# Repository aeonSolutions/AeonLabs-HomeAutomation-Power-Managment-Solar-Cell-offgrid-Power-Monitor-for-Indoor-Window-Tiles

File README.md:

[PCB-Prototyping-Catalogue](https://github.com/aeonSolutions/PCB-Prototyping-Catalogue)  >>  [Home-Automation](https://github.com/aeonSolutions/PCB-Prototyping-Catalogue/tree/main/Home-Automation)  >>  [Smart Home Solar Power Management](https://github.com/aeonSolutions/PCB-Prototyping-Catalogue/tree/main/Home-Automation/Smart%20Home%20Solar%20Power%20Management)  >>   Solar Cell Tiles Power Monitor for Indoor Windows

<br>

<br />

# Solar Cell Tiles Power Monitor for Indoor Windows

This is a simple PCB for a direct fit on commercially available [blue solar cell tiles](https://s.click.aliexpress.com/e/_DCnJW0V)  with dimensions 124x124mm. This Smart Device is intended to connected with the [Single Solar Cell with one 18650 Battery Storage](https://github.com/aeonSolutions/AeonLabs-HomeAutomation-Power-Managment-Single-SolarCELL-18650-battery-storage/blob/main/README.md) and also the [Single Solar Cell with two 18650 as Battery Storage](https://github.com/aeonSolutions/AeonLabs-HomeAutomation-Power-Managment-Single-SolarCELL-2X-18650-battery-storage/blob/main/README.md) to do active solar cell tile and battery management up to 8 solar tiles conencted together intended for indoor usage. In particular to be installed on the top or downside of transparent glass windows at a home or office. This PCB, when assembled with a blue solar cell tile, can be used to power a low voltage 4.2V indoor illumination network using ultra-low power micro LED strips.  For insatnce [this one](https://s.click.aliexpress.com/e/_DCKg9xJ) sold on AliExpress.   

When connected in series and installed on several windows and networked, can power off the grid a 4.2V LED illumination on all rooms and compartments at a home or office. During evenings and at night until bedtime. If one intends to use it to power indoors LED illumination during the day is required a High Capacity Power Bank connected to all first tiles of all the series. For instance this [power bank](https://s.click.aliexpress.com/e/_Ddl7nsh) here. 

One important take way about this prototype project is in the ability to be installed on any traditional apartment or home in a big city, requiring  124mm of window glass estate, at the top or at the bottom. And it can connect to existing home automation network or systems. 

<p align="center">

</p>

A breif view of specifications:

- up to 8 solar cell tiles battery active monitoring 
- Buzzer for sound alarm and warnings
- Onboard Temperature and humidity sensores
- Onboard motion sensor
- PCB asssembly in series made with a 10 pin pin header/ socket. For "plug and play" type of instalations
- Screw terminal to connect main low power 5V DC line at home/office. 

<br>

**Status**

waiting to be tested. Stay tuned for updates.

<br>

## PCB

<br>

## Compatibility

<p align="center">

</p>

<br>

## What one additionally needs
-  home tools
-  [transparent double sided tape](https://s.click.aliexpress.com/e/_DDJxMmD)
-  [blue solar cell tiles](https://s.click.aliexpress.com/e/_DCnJW0V)
-  [ultra-low power micro LED strips](https://s.click.aliexpress.com/e/_DCKg9xJ) 
-  [ultra-low power  LED Cob strips](https://s.click.aliexpress.com/e/_DnqkC4N)
-  [Nylon Guide for Electric Cable](https://s.click.aliexpress.com/e/_DBc1oVX)
-  [NCR18650B 3.7V 3400 mah 18650 Lithium](https://s.click.aliexpress.com/e/_DCh1sw1)
-  [Low power electrical wire](https://s.click.aliexpress.com/e/_DB1T3eN)
-  [16A Electrical Plug Wall Socket 110~250V Dual USB 2000mA Port](https://s.click.aliexpress.com/e/_DlVz3sh)
-  [Soldering iron](https://s.click.aliexpress.com/e/_DnDN8x3)
-  [Solder](https://s.click.aliexpress.com/e/_DlXtKMN)
- [power bank](https://s.click.aliexpress.com/e/_Ddl7nsh) 

<br />
<br />

## Author

You can get in touch with me on my LinkedIn Profile:

#### Miguel Tomas

You can also follow my GitHub Profile to stay updated about my latest projects: 

<br>

### Be supportive of my dedication and work towards technology education and buy me a cup of coffee
The PCB Desgin Files i provide here for anyone to use are free. If you like this Smart Device or use it, please consider buying me a cup of coffee, a slice of pizza or a book to help me study, eat and think new PCB design files.

<br />

### Make a donation on Paypal
Make a donation on paypal and get a TAX refund*.

<br>

### Support all these open hardware projects and become a patreon  
Liked any of my PCB KiCad Designs? Help and Support my open work to all by becomming a LDAD Patreon.
In return I will give a free PCB design in KiCad to all patreon supporters. To learn more go to patreon.com. Link below.

<br />
<br />

______________________________________________________________________________________________________________________________
### License
Before proceeding to download any of AeonLabs software solutions for open-source development and/or PCB hardware electronics development make sure you are choosing the right license for your project. See [AeonLabs Solutions for Open Hardware & Source Development](https://github.com/aeonSolutions/PCB-Prototyping-Catalogue/wiki/AeonLabs-Solutions-for-Open-Hardware-&-Source-Development) for more information.

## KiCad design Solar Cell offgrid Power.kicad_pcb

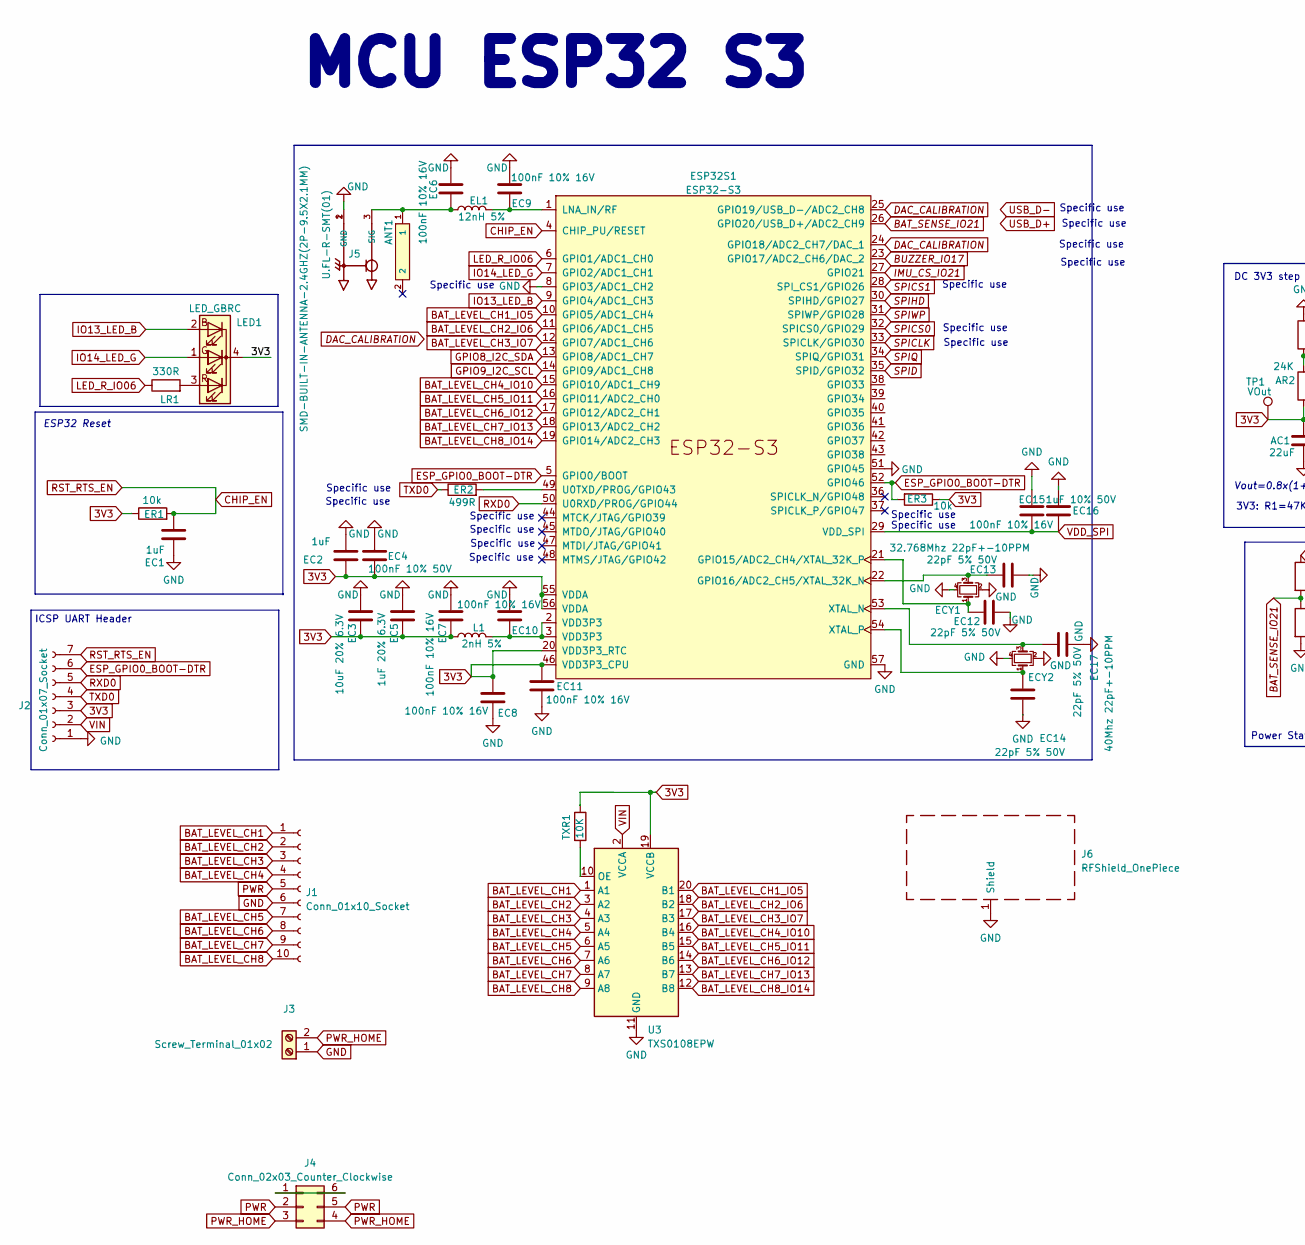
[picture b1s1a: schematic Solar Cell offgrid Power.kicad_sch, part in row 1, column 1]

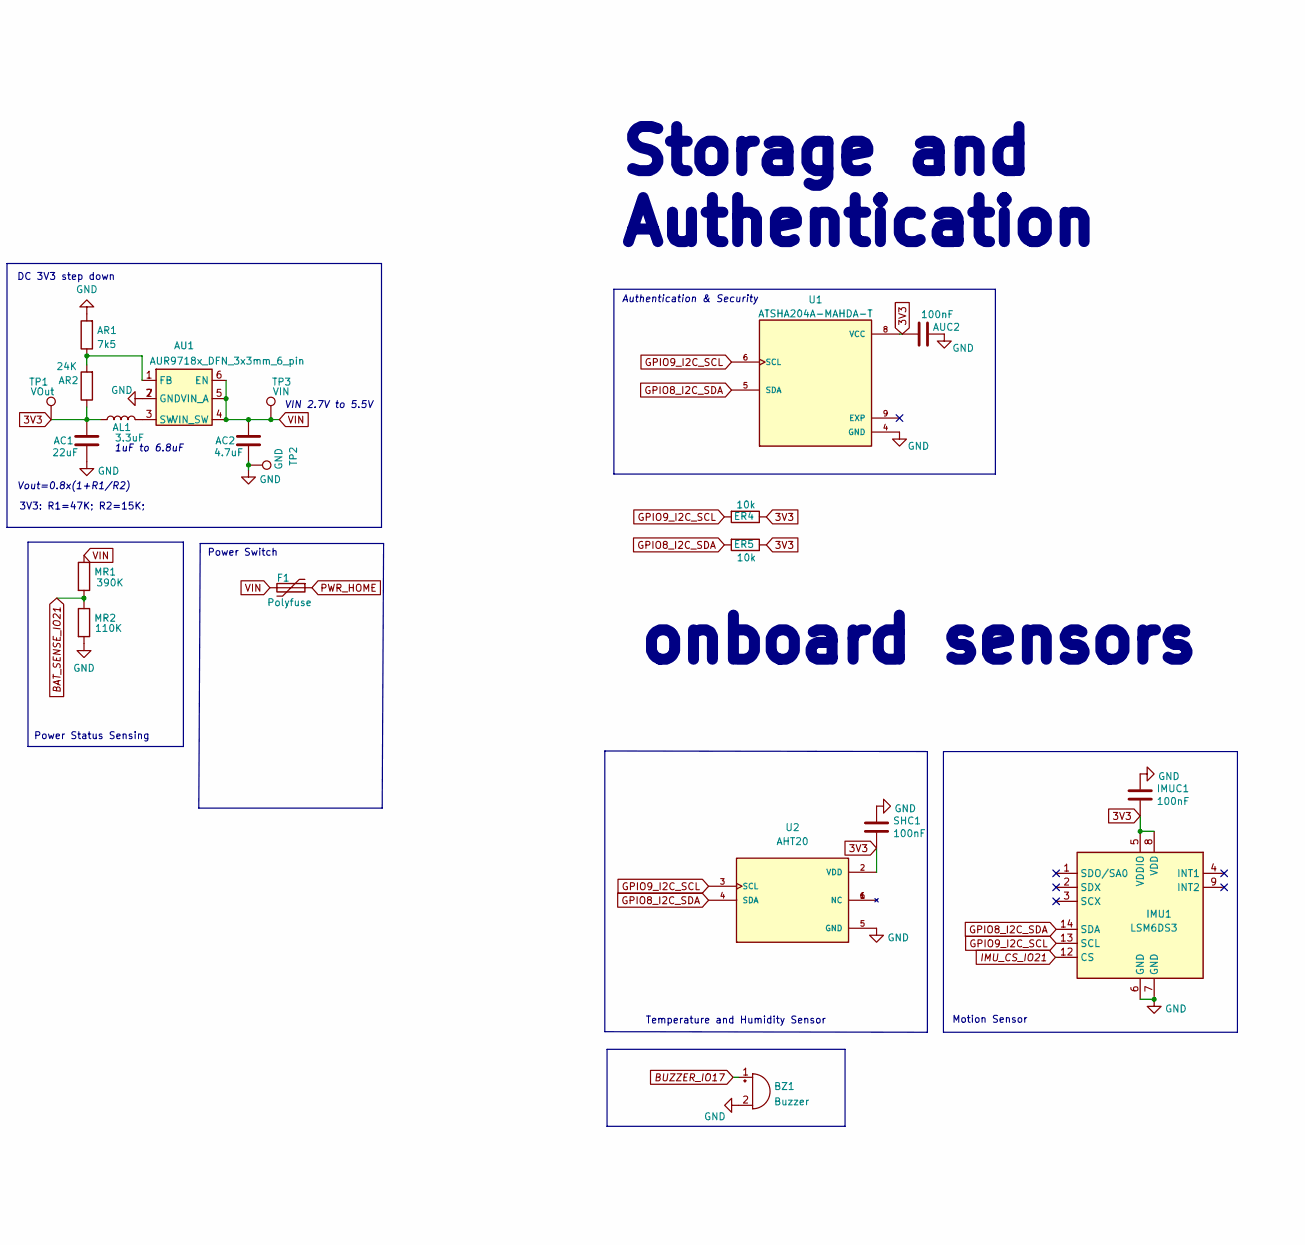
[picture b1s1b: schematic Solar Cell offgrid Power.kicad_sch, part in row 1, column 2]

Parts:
AC1: 22uF; C_0805_2012Metric_Pad1.18x1.45mm_HandSolder
AC2: 4.7uF; C_0805_2012Metric_Pad1.18x1.45mm_HandSolder
AL1: 3.3uF; L_1210_3225Metric
ANT1: SMD-BUILT-IN-ANTENNA-2.4GHZ(2P-9.5X2.1MM); 2.4ghZ WIFI ANTENNA AN9520_ANT2-SMD-9.5X2.1X1.0MM
AR1: 7k5; R_0805_2012Metric_Pad1.20x1.40mm_HandSolder
AR2: 24K; R_0805_2012Metric_Pad1.20x1.40mm_HandSolder
AU1: AUR9718x_DFN_3x3mm_6_pin; AUR9718 ST1S09 SON95P300X300X100-7N
AUC2: 100nF; C_0603_1608Metric
BZ1: Buzzer; MagneticBuzzer_Kobitone_254-EMB84Q-RO
EC1: 1uF; C_0603_1608Metric
EC2: 1uF; C_0805_2012Metric
EC3: 10uF 20% 6.3V; C_0805_2012Metric
EC4: 100nF 10% 50V; C_0603_1608Metric
EC5: 1uF 20% 6.3V; C_0603_1608Metric
EC6, EC7, EC8, EC9, EC10, EC11, EC15: 100nF 10% 16V; C_0603_1608Metric
EC12, EC13, EC14, EC17: 22pF 5% 50V; C_0603_1608Metric
EC16: 1uF 10% 50V; C_0603_1608Metric
ECY1: 32.768Mhz 22pF+-10PPM; Crystal_SMD_EuroQuartz_MT-4Pin_3.2x2.5mm
ECY2: 40Mhz 22pF+-10PPM; Crystal_SMD_EuroQuartz_MT-4Pin_3.2x2.5mm
EL1: 12nH 5%; L_0805_2012Metric
ER1, ER3, ER4, ER5: 10k; R_0603_1608Metric
ER2: 499R; R_0603_1608Metric
ESP32S1: ESP32-S3; QFN-56-1EP_7x7mm_P0.4mm_EP5.6x5.6mm
F1: Polyfuse; Fuse_1206_3216Metric_Pad1.42x1.75mm_HandSolder
IMU1: LSM6DS3; LSM6DS3 Motion Sensor PQFN50P300X250X86-14N
IMUC1: 100nF; C_0603_1608Metric
J1: Conn_01x10_Socket; PinSocket_1x10_P2.54mm_Horizontal
J2: Conn_01x07_Socket; JST_SH_SM07B-SRSS-TB_1x07-1MP_P1.00mm_Horizontal
J3: Screw_Terminal_01x02; TerminalBlock_Phoenix_MPT-0,5-2-2.54_1x02_P2.54mm_Horizontal
J4: Conn_02x03_Counter_Clockwise; Toggle Switch 2 pos PCB MSS-22D18G2 2P2T
J5: U.FL-R-SMT(01); RF Antenna IPEX SMD PCB HRS_U.FL-R-SMT(01)
J6: RFShield_OnePiece; ESP32-S3 GND Shield
L1: 2nH 5%; L_0805_2012Metric
LED1: LED_GBRC; LED_1206_3210_RGB_Metric
LR1: 330R; R_0603_1608Metric
MR1: 390K; R_0603_1608Metric
MR2: 110K; R_0603_1608Metric
SHC1: 100nF; C_0603_1608Metric
TP1: VOut; TestPoint_Pad_D1.0mm
TP2: GND; TestPoint_Pad_D1.0mm
TP3: VIN; TestPoint_Pad_D1.0mm
TXR1: 10K; R_0603_1608Metric
U1: ATSHA204A-MAHDA-T; ATSHA204A Auth SOIC8; PART_REV A
U2: AHT20; AHT20 HT Sensor PSON100P300X300X110-6N; PARTREV V1.0
U3: TXS0108EPW; TSSOP-20_4.4x6.5mm_P0.65mm

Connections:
3V3: AC1.1, AL1.1, AR2.1, EC2.2, EC3.1, EC4.2, EC5.1, EC7.1, EC8.1, EC11.1, ER1.1, ER3.1, ER4.1, ER5.1, ESP32S1.20 (VDD3P3_RTC), ESP32S1.46 (VDD3P3_CPU), ESP32S1.55 (VDDA), ESP32S1.56 (VDDA), IMU1.5 (VDDIO), IMU1.8 (VDD), IMUC1.2, J2.3, L1.1, LED1.4 (K), SHC1.2, TP1.1, TXR1.1, U1.8 (VCC), U2.2 (VDD), U3.19 (VCCB)
BAT_LEVEL_CH1: J1.1, U3.1 (A1)
BAT_LEVEL_CH1_IO5: ESP32S1.10 (GPIO5/ADC1_CH4), U3.20 (B1)
BAT_LEVEL_CH2: J1.2, U3.3 (A2)
BAT_LEVEL_CH2_IO6: ESP32S1.11 (GPIO6/ADC1_CH5), U3.18 (B2)
BAT_LEVEL_CH3: J1.3, U3.4 (A3)
BAT_LEVEL_CH3_IO7: ESP32S1.12 (GPIO7/ADC1_CH6), U3.17 (B3)
BAT_LEVEL_CH4: J1.4, U3.5 (A4)
BAT_LEVEL_CH4_IO10: ESP32S1.15 (GPIO10/ADC1_CH9), U3.16 (B4)
BAT_LEVEL_CH5: J1.7, U3.6 (A5)
BAT_LEVEL_CH5_IO11: ESP32S1.16 (GPIO11/ADC2_CH0), U3.15 (B5)
BAT_LEVEL_CH6: J1.8, U3.7 (A6)
BAT_LEVEL_CH6_IO12: ESP32S1.17 (GPIO12/ADC2_CH1), U3.14 (B6)
BAT_LEVEL_CH7: J1.9, U3.8 (A7)
BAT_LEVEL_CH7_IO13: ESP32S1.18 (GPIO13/ADC2_CH2), U3.13 (B7)
BAT_LEVEL_CH8: J1.10, U3.9 (A8)
BAT_LEVEL_CH8_IO14: ESP32S1.19 (GPIO14/ADC2_CH3), U3.12 (B8)
BAT_SENSE_IO21: ESP32S1.26 (GPIO20/USB_D+/ADC2_CH9), MR1.2, MR2.1
BUZZER_IO17: BZ1.1 (-), ESP32S1.23 (GPIO17/ADC2_CH6/DAC_2)
CHIP_EN: EC1.2, ER1.2, ESP32S1.4 (CHIP_PU/RESET), J2.7
DAC_CALIBRATION: ESP32S1.24 (GPIO18/ADC2_CH7/DAC_1), ESP32S1.25 (GPIO19/USB_D-/ADC2_CH8)
ESP_GPIO0_BOOT-DTR: ER3.2, ESP32S1.5 (GPIO0/BOOT), ESP32S1.52 (GPIO46), J2.6
GND: AC1.2, AC2.2, AR1.2, AU1.2 (GND), AU1.7 (GND), BZ1.2 (+), EC1.1, EC2.1, EC3.2, EC4.1, EC5.2, EC6.2, EC7.2, EC8.2, EC9.2, EC10.2, EC11.2, EC12.2, EC13.2, EC14.2, EC17.2, ECY1.2, ECY1.4, ECY2.2, ECY2.4, ESP32S1.8 (GPIO3/ADC1_CH2), ESP32S1.51 (GPIO45), ESP32S1.57 (GND), IMU1.6 (GND), IMU1.7 (GND), IMUC1.1, J1.6, J2.1, J3.1, J5.1 (GND), J5.2 (GND), J6.1 (Shield), MR2.2, SHC1.1, TP2.1, U1.4 (GND), U2.5 (GND), U3.11 (GND)
GPIO8_I2C_SDA: ER5.2, ESP32S1.13 (GPIO8/ADC1_CH7), IMU1.14 (SDA), U1.5 (SDA), U2.4 (SDA)
GPIO9_I2C_SCL: ER4.2, ESP32S1.14 (GPIO9/ADC1_CH8), IMU1.13 (SCL), U1.6 (SCL), U2.3 (SCL)
IMU_CS_IO21: ESP32S1.27 (GPIO21), IMU1.12 (CS)
IO13_LED_B: ESP32S1.9 (GPIO4/ADC1_CH3), LED1.2 (BA)
IO14_LED_G: ESP32S1.7 (GPIO2/ADC1_CH1), LED1.1 (GA)
LED_R_IO06: ESP32S1.6 (GPIO1/ADC1_CH0), LR1.1
unnamed: AR1.1, AR2.2, AU1.1 (FB)
unnamed: AL1.2, AU1.3 (SW)
unnamed: EC10.1, ESP32S1.2 (VDD3P3), ESP32S1.3 (VDD3P3), L1.2
unnamed: EC12.1, ECY1.1, ESP32S1.21 (GPIO15/ADC2_CH4/XTAL_32K_P)
unnamed: EC13.1, ECY1.3, ESP32S1.22 (GPIO16/ADC2_CH5/XTAL_32K_N)
unnamed: EC9.1, EL1.2, ESP32S1.1 (LNA_IN/RF)
unnamed: ER2.2, ESP32S1.49 (U0TXD/PROG/GPIO43)
unnamed: EC17.1, ECY2.3, ESP32S1.53 (XTAL_N)
unnamed: EC14.1, ECY2.1, ESP32S1.54 (XTAL_P)
unnamed: J4.1, J4.6
unnamed: ANT1.1, EC6.1, EL1.1, J5.3 (SIG)
unnamed: LED1.3 (RA), LR1.2
unnamed: TXR1.2, U3.10 (OE)
PWR: J1.5, J4.2, J4.5
PWR_HOME: F1.1, J3.2, J4.3, J4.4
RXD0: ESP32S1.50 (U0RXD/PROG/GPIO44), J2.5
SPICLK: ESP32S1.33 (SPICLK/GPIO30)
SPICS0: ESP32S1.32 (SPICS0/GPIO29)
SPICS1: ESP32S1.28 (SPI_CS1/GPIO26)
SPID: ESP32S1.35 (SPID/GPIO32)
SPIHD: ESP32S1.30 (SPIHD/GPIO27)
SPIQ: ESP32S1.34 (SPIQ/GPIO31)
SPIWP: ESP32S1.31 (SPIWP/GPIO28)
TXD0: ER2.1, J2.4
VDD_SPI: EC15.1, EC16.1, ESP32S1.29 (VDD_SPI)
VIN: AC2.1, AU1.4 (VIN_SW), AU1.5 (VIN_A), AU1.6 (EN), F1.2, J2.2, MR1.1, TP3.1, U3.2 (VCCA)

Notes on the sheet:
Specific use
Vout=0.8x(1+R1/R2)
onboard sensors
3V3: R1=47K; R2=15K;
Power Status Sensing
DC 3V3 step down
ESP32 Reset
Authentication & Security
Storage and Authentication
VIN 2.7V to 5.5V
Temperature and Humidity Sensor
Power Switch
ICSP UART Header
1uF to 6.8uF
MCU ESP32 S3
Motion Sensor

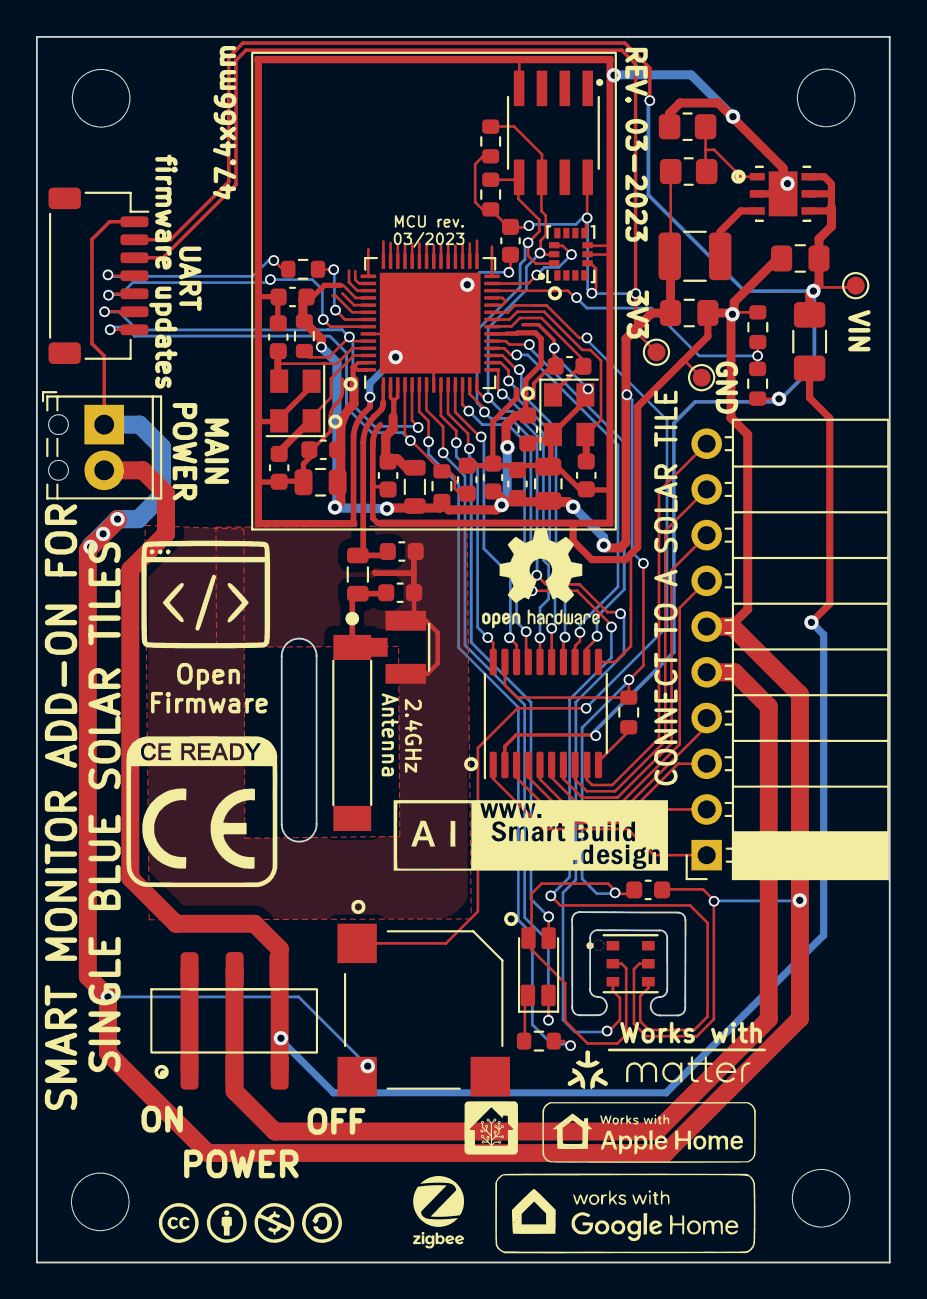
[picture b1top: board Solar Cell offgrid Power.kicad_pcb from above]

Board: 2 copper layers, 47.4 x 68.1 mm, 54 parts (0 on the bottom side), 47 nets.
